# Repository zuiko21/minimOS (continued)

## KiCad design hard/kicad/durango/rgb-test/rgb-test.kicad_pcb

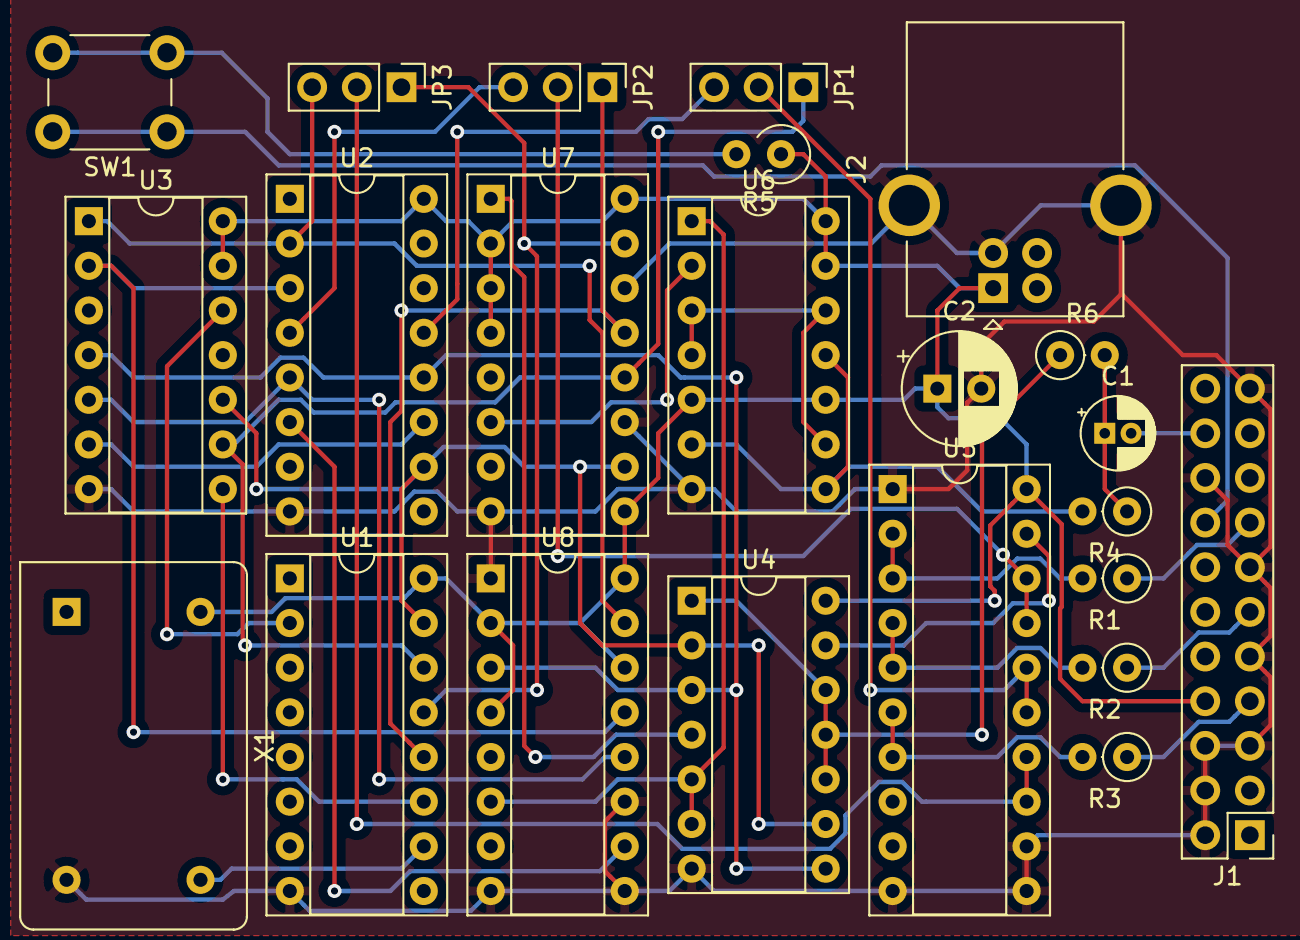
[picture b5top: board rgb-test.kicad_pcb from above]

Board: 2 copper layers, 23 parts (0 on the bottom side), 37 nets.

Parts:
C1: 100uF; CP_Radial_D4.0mm_P1.50mm
C2: 470uF; CP_Radial_D6.3mm_P2.50mm
J1: SCART; PinHeader_2x11_P2.54mm_Vertical
J2: POWER; USB_B_OST_USB-B1HSxx_Horizontal
JP1: GREEN SEL; PinHeader_1x03_P2.54mm_Vertical
JP2: RED SEL; PinHeader_1x03_P2.54mm_Vertical
JP3: BLUE SEL; PinHeader_1x03_P2.54mm_Vertical
R1, R2, R3: 470; R_Axial_DIN0207_L6.3mm_D2.5mm_P2.54mm_Vertical
R4: 1K2; R_Axial_DIN0207_L6.3mm_D2.5mm_P2.54mm_Vertical
R5: 180; R_Axial_DIN0309_L9.0mm_D3.2mm_P2.54mm_Vertical
R6: 1K5; R_Axial_DIN0207_L6.3mm_D2.5mm_P2.54mm_Vertical
SW1: TEST; SW_PUSH_6mm
U1: 74HCT4040; DIP-16_W7.62mm_Socket
U2: 74HC4040; DIP-16_W7.62mm_Socket
U3: 74HC21; DIP-14_W7.62mm_Socket
U4: 74HC02; DIP-14_W7.62mm_Socket
U5: 74HC245; DIP-20_W7.62mm_Socket
U6: 74HC86; DIP-14_W7.62mm_Socket
U7, U8: 74HC85; DIP-16_W7.62mm_Socket
X1: 24.576 MHz; Oscillator_DIP-14

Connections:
+5V: C2.1, J1.8, J2.1, R5.1, U1.16, U2.16, U3.13, U3.14, U4.14, U5.20, U6.5, U6.10, U6.13, U6.14, U7.2, U7.3, U7.4, U7.9, U7.16, U8.2, U8.4, U8.14, U8.16, X1.14
/BIN: JP3.2, U5.13, U5.14
/BLUE: R3.2, U5.6, U5.7
/COMP: C1.2, J1.20
/CSYNC: U6.3, U6.4, U6.9, U6.12
/DE: R6.1, U4.1, U4.10, U4.11, U4.12
/FB: J1.16, SW1.1
/FEND: U2.11, U3.6
/GIN: JP1.2, U5.15, U5.16
/GREEN: R2.2, U5.4, U5.5
/H0: JP3.1, U1.13, U7.15
/H1: JP2.1, U1.12, U7.13
/H2: JP1.1, U1.14, U3.9, U7.12
/HS: U6.2, U7.6
/LEND: U1.11, U3.8
/RED: R1.2, U5.2, U5.3
/RIN: JP2.2, U5.17, U5.18
/S_B: J1.7, R3.1
/S_G: J1.11, R2.1
/S_R: J1.15, R1.1
/V0: JP3.3, U2.2, U3.1, U8.15
/V1: JP2.3, U2.4
/V2: JP1.3, U2.13
/VA1: U1.2, U3.12
/VS: U4.5, U4.6, U6.1, U8.6
/~CSYNC: R4.2, U6.6, U6.8, U6.11
/~DE: U4.13, U5.19
/~DEH: U1.15, U2.10, U3.10, U4.2, U4.9, U7.10
/~DEV: U2.12, U3.4, U4.3, U4.8, U8.3
/~S_SYNC: C1.1, R4.1, R6.2
/~VS: U4.4, U7.1
GND: C2.2, J1.2, J1.4, J1.5, J1.6, J1.9, J1.13, J1.18, J1.21, J2.4, J2.5, U1.8, U2.8, U3.7, U4.7, U5.1, U5.10, U5.11, U5.12, U6.7, U7.8, U7.11, U7.14, U8.1, U8.8, U8.9, U8.11, X1.7
unnamed: R5.2, SW1.2
unnamed: U1.10, X1.8
unnamed: U2.3, U3.2, U8.13
unnamed: U2.5, U3.5, U8.12
unnamed: U2.6, U8.10

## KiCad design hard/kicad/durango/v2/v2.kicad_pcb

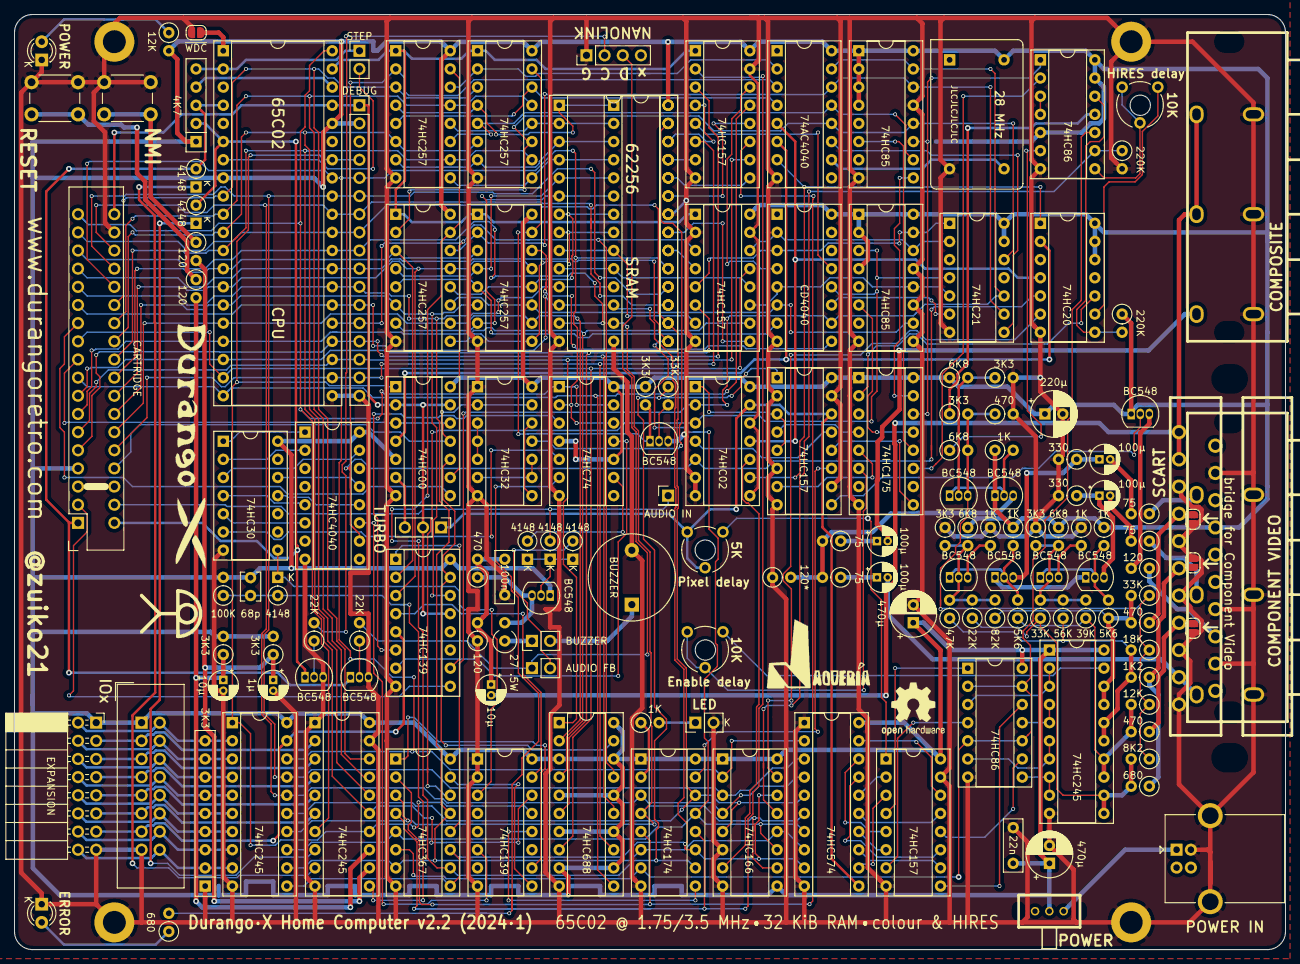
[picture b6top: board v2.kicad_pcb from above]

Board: 2 copper layers, 177.8 x 130.8 mm, 159 parts (0 on the bottom side), 218 nets.

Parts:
BZ1: BUZZER; Buzzer_12x9.5RM7.6
C1, C3: 10µ; CP_Radial_D4.0mm_P1.50mm
C2: 100n; C_Rect_L7.2mm_W2.5mm_P5.00mm_FKS2_FKP2_MKS2_MKP2
C4: 220µ; CP_Radial_D6.3mm_P2.50mm
C5, C611, C612, C709: 100µ; CP_Radial_D4.0mm_P1.50mm
C6, C613: 470µ; CP_Radial_D6.3mm_P2.50mm
C7: 22n; C_Rect_L7.2mm_W2.5mm_P5.00mm_FKS2_FKP2_MKS2_MKP2
C8: 68p; C_Disc_D3.8mm_W2.6mm_P2.50mm
C10: 1µ; CP_Radial_D4.0mm_P1.50mm
D1, D2, D3, D5, D7, D8: 4148; D_DO-35_SOD27_P2.54mm_Vertical_KathodeUp
D4: ERROR; LED_D3.0mm_Clear
D6: POWER; LED_D3.0mm_Clear
H1, H2, H3, H4: MountingHole_3.2mm_M3_DIN965_Pad
J1: NANOLINK; PinHeader_1x04_P2.54mm_Vertical
J2: AUDIO IN; PinHeader_1x01_P2.54mm_Vertical
J3: IOx; IDC-Header_2x08_P2.54mm_Vertical
J4: LED; PinHeader_1x02_P2.54mm_Vertical
J7: POWER IN; USB_B_OST_USB-B1HSxx_Horizontal
J8: DEBUG; PinSocket_1x17_P2.54mm_Vertical
J9: CARTRIDGE; PinSocket_2x18_EDGE
J10: STEP; PinHeader_1x02_P2.54mm_Vertical
J11: EXPANSION; PinSocket_2x08_P2.54mm_Horizontal
J605: COMPONENT VIDEO; 3xRCA
J706: COMPOSITE; 3xRCA
J905: SCART
JP1: AUDIO FB; PinHeader_1x02_P2.54mm_Vertical
JP2: BUZZER; PinHeader_1x02_P2.54mm_Vertical
JP3: POWER; PowerSwitch
JP4: ~WDC; SolderJumper-2_P1.3mm_Open_RoundedPad1.0x1.5mm
JP5: TURBO; PinHeader_1x03_P2.54mm_Vertical
JP606: bridge for Component Video; SolderJumper-2_P1.3mm_Open_RoundedPad1.0x1.5mm
JP607, JP608: CV; SolderJumper-2_P1.3mm_Open_RoundedPad1.0x1.5mm
LOGO1: OSHW-Logo2_9.8x8mm_SilkScreen
LOGO2: durango-x90
LOGO3: jaqueria
Q1, Q2, Q3, Q4, Q5, Q307, Q608, Q609, Q610, Q611, Q906: BC548; TO-92_Inline
R1, R2, R644: 22K; R_Axial_DIN0207_L6.3mm_D2.5mm_P2.54mm_Vertical
R3, R18, R34, R220, R337, R639, R649: 3K3; R_Axial_DIN0207_L6.3mm_D2.5mm_P2.54mm_Vertical
R4, R21, R112, R114: 470; R_Axial_DIN0207_L6.3mm_D2.5mm_P2.54mm_Vertical
R5, R33, R35, R922: 120; R_Axial_DIN0207_L6.3mm_D2.5mm_P2.54mm_Vertical
R6, R111: 680; R_Axial_DIN0207_L6.3mm_D2.5mm_P2.54mm_Vertical
R15: 120*; R_Axial_DIN0207_L6.3mm_D2.5mm_P2.54mm_Vertical
R16, R32, R640, R641, R650, R651: 1K; R_Axial_DIN0207_L6.3mm_D2.5mm_P2.54mm_Vertical
R17, R19, R638, R648: 6K8; R_Axial_DIN0207_L6.3mm_D2.5mm_P2.54mm_Vertical
R23: 27 .5W; R_Axial_DIN0309_L9.0mm_D3.2mm_P2.54mm_Vertical
R26: 100K; R_Axial_DIN0207_L6.3mm_D2.5mm_P2.54mm_Vertical
R29, R108: 12K; R_Axial_DIN0207_L6.3mm_D2.5mm_P2.54mm_Vertical
R30, R647, R657, R731: 75; R_Axial_DIN0207_L6.3mm_D2.5mm_P2.54mm_Vertical
R107: 8K2; R_Axial_DIN0207_L6.3mm_D2.5mm_P2.54mm_Vertical
R109: 18K; R_Axial_DIN0207_L6.3mm_D2.5mm_P2.54mm_Vertical
R110, R336, R654: 33K; R_Axial_DIN0207_L6.3mm_D2.5mm_P2.54mm_Vertical
R113: 1K2; R_Axial_DIN0207_L6.3mm_D2.5mm_P2.54mm_Vertical
R642, R652: 330; R_Axial_DIN0207_L6.3mm_D2.5mm_P2.54mm_Vertical
R643, R653: 5K6; R_Axial_DIN0207_L6.3mm_D2.5mm_P2.54mm_Vertical
R645: 47K; R_Axial_DIN0207_L6.3mm_D2.5mm_P2.54mm_Vertical
R646: 82K; R_Axial_DIN0207_L6.3mm_D2.5mm_P2.54mm_Vertical
R655: 56K; R_Axial_DIN0207_L6.3mm_D2.5mm_P2.54mm_Vertical
R656: 39K; R_Axial_DIN0207_L6.3mm_D2.5mm_P2.54mm_Vertical
R824, R825: 220K; R_Axial_DIN0207_L6.3mm_D2.5mm_P2.54mm_Vertical
RN1: 4K7; R_Array_SIP5
RN2: 3K3; R_Array_SIP9
RV127: 5K; Potentiometer_Piher_PT-6-V_Vertical
RV128, RV231: 10K; Potentiometer_Piher_PT-6-V_Vertical
SW1: RESET; SW_PUSH_6mm
SW2: NMI; SW_PUSH_6mm
U1: 65C02; DIP-40_W15.24mm_Socket
U003: 62256; DIP-28_W7.62mm_Socket
U3: 62256; DIP-28_W15.24mm_Socket
U6, U7, U125, U321: 74HC157; DIP-16_W7.62mm_Socket
U8: 74HC30; DIP-14_W7.62mm_Socket
U9: 74HC00; DIP-14_W7.62mm_Socket
U10, U29: 74HC139; DIP-16_W7.62mm_Socket
U11: 74HC688; DIP-20_W7.62mm_Socket
U12: 74HC74; DIP-14_W7.62mm_Socket
U13: 74HC32; DIP-14_W7.62mm_Socket
U14: 74HC4040; DIP-16_W7.62mm_Socket
U15: 74AC4040; DIP-16_W7.62mm_Socket
U16: 74HC02; DIP-14_W7.62mm_Socket
U17: 74HC21; DIP-14_W7.62mm_Socket
U18, U20: 74HC85; DIP-16_W7.62mm_Socket
U19: CD4040; DIP-16_W7.62mm_Socket
U22: 74HC175; DIP-16_W7.62mm_Socket
U23, U126: 74HC86; DIP-14_W7.62mm_Socket
U31, U32, U127: 74HC245; DIP-20_W7.62mm_Socket
U104, U105, U204, U205: 74HC257; DIP-16_W7.62mm_Socket
U124: 74HC574; DIP-20_W7.62mm_Socket
U224: 74HC166; DIP-16_W7.62mm_Socket
U227: 74HC20; DIP-14_W7.62mm_Socket
U428: 74HC174; DIP-16_W7.62mm_Socket
U530: 74HC367; DIP-16_W7.62mm_Socket
X1: 28 MHz; Oscillator_DIP-14

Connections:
+5V: C4.1, C6.1, C7.1, C8.2, C613.1, J3.1, J8.2, J9.7, J11.1, J905.8, JP3.2, Q3.1, Q5.1, Q609.1, Q611.1, Q906.1, R3.2, R16.1, R17.1, R26.2, R29.2, R34.2, R337.1, R638.1, R641.1, R648.1, R651.1, R825.1, RN1.1, U1.8, U1.36, U003.28, U3.28, U6.16, U7.16, U8.14, U9.5, U9.14, U10.16, U11.3, U11.5, U11.7, U11.9, U11.12, U11.14, U11.16, U11.18, U11.20, U12.4, U12.10, U12.14, U13.14, U14.16, U15.16, U16.14, U17.13, U17.14, U18.1, U18.2, U18.3, U18.4, U18.16, U19.16, U20.1, U20.2, U20.4, U20.16, U22.1, U22.16, U23.5, U23.13, U23.14, U29.16, U31.20, U32.20, U104.16, U105.16, U124.20, U125.16, U126.14, U127.1, U127.20, U204.16, U205.16, U224.1, U224.9, U224.16, U227.12, U227.13, U227.14, U321.16, U428.1, U428.16, U530.16, X1.14
/250HZ: U14.11, U29.6
/ABUF: Q3.3, R4.1, R23.2
/AFB: D7.2, JP1.2
/AFILT: C2.1, C3.1, R4.2, R5.2
/AMIX: D2.1, D3.1, D7.1, Q3.2
/AOUT: D2.2, U12.9
/ATBZ: JP2.1, R23.1
/BCL: Q2.2, R2.1
/BDT: Q1.2, R1.1
/BZZ: BZ1.1, JP2.2
/CNT1K: U8.3, U14.15
/CNT2K: U8.1, U14.1
/CNT4: U8.5, U14.6
/CNT8: U8.4, U14.5
/CNT32: U8.2, U14.2
/CNT128: U8.12, U14.13
/CNT256: U8.11, U14.12
/ERRLED: D4.2, R6.1
/HR_B: Q307.2, R336.2
/IEN: U8.6, U12.5
/PHI2: U1.39, U6.1, U7.1, U104.1, U105.1, U204.1, U205.1
/PWLED: D6.2, R29.1
/Power and Extras/+5V_IN: J7.1, JP3.3
/Power and Extras/B_BIAS: Q610.2, R648.2, R649.2, R654.2, R655.2, R656.2
/Power and Extras/B_BUF: C612.1, Q611.3, R652.1
/Power and Extras/EB: Q610.3, R650.2
/Power and Extras/ER: Q608.3, R640.2
/Power and Extras/LED_R: J4.1, R32.2
/Power and Extras/N_SW: R35.1, SW2.2
/Power and Extras/PB: J605.3, R657.1
/Power and Extras/PB_C: C612.2, R657.2
/Power and Extras/PR: J605.1, R647.1
/Power and Extras/PR_C: C611.2, R647.2
/Power and Extras/RMIX2: C709.1, R731.1
/Power and Extras/R_BIAS: Q608.2, R638.2, R639.2, R644.2, R645.2, R646.2
/Power and Extras/R_BUF: C611.1, Q609.3, R642.1
/Power and Extras/R_SW: R33.1, SW1.1
/Power and Extras/UB: Q610.1, Q611.2, R651.2, R653.2
/Power and Extras/UR: Q608.1, Q609.2, R641.2, R643.2
/Power and Extras/Y: C709.2, J706.5
/Power and Extras/~ANMI: C10.1, R34.1, R35.2, U32.12
/Power and Extras/~ARST: C1.1, R3.1, R33.2, U32.13
/Power and Extras/~ST250: C8.1, D5.2, R26.1, U32.11
/RDY: J10.1, RN1.5, U1.2
/SERCLK: J1.2, R2.2
/SERDAT: J1.3, JP1.1, R1.2
/SYNC: J10.2, U1.7
/Video & Clock generation/BIAS: Q4.2, R17.2, R18.1
/Video & Clock generation/BLUE: J905.7, JP608.1, R114.1
/Video & Clock generation/BUFRGB: Q906.3, R922.2
/Video & Clock generation/B_L: U124.12, U125.3
/Video & Clock generation/B_R: U124.16, U125.2
/Video & Clock generation/COLOUR: U321.11, U428.15
/Video & Clock generation/CSYNC: U23.3, U23.4
/Video & Clock generation/DE: U16.1, U321.3, U321.5
/Video & Clock generation/DEV~ODD: RV127.3, U125.1
/Video & Clock generation/DHRDE: U22.2, U227.10
/Video & Clock generation/DHVD: RV231.3, U227.9
/Video & Clock generation/FBLANK: J905.16, R922.1
/Video & Clock generation/FEND: U17.6, U19.11
/Video & Clock generation/GH_L: U124.15, U125.13
/Video & Clock generation/GH_R: U124.19, U125.14
/Video & Clock generation/GL_L: U124.13, U125.10
/Video & Clock generation/GL_R: U124.17, U125.11
/Video & Clock generation/GRN: J905.11, JP607.1, R111.1, R113.1
/Video & Clock generation/HDOT: U16.10, U224.7
/Video & Clock generation/HPIX: R824.1, U23.9, U224.13
/Video & Clock generation/HVG: R220.1, U23.11
/Video & Clock generation/HVID: RV231.1, RV231.2, U23.8
/Video & Clock generation/IB: U126.3, U127.2, U127.3
/Video & Clock generation/IGH: U126.8, U127.8, U127.9
/Video & Clock generation/IGL: U126.11, U127.4, U127.5
/Video & Clock generation/IR: U126.6, U127.6, U127.7
/Video & Clock generation/LATCH: U22.9, U321.12
/Video & Clock generation/LEND: U15.11, U17.8
/Video & Clock generation/MCLK: U15.10, X1.8
/Video & Clock generation/Q1: U15.7, U16.9, U227.1
/Video & Clock generation/Q3: U15.5, U16.11, U227.4
/Video & Clock generation/RED: J905.15, JP606.1, R112.1
/Video & Clock generation/RGB: Q906.2, U321.9
/Video & Clock generation/RMIX: C5.1, R30.1
/Video & Clock generation/R_L: U124.14, U125.6
/Video & Clock generation/R_R: U124.18, U125.5
/Video & Clock generation/UCDE: U22.5, U321.7
/Video & Clock generation/UHDE: U22.4, U321.4
/Video & Clock generation/UHS: U18.6, U22.12
/Video & Clock generation/UVS: U20.6, U22.13
/Video & Clock generation/VIN: Q4.3, R19.2, R21.1, R107.1, R108.1, R109.1, R110.1, R220.2
/Video & Clock generation/VS: U18.9, U22.15
/Video & Clock generation/XB: U125.4, U126.1
/Video & Clock generation/XGH: U125.12, U126.9
/Video & Clock generation/XGL: U125.9, U126.12
/Video & Clock generation/XR: U125.7, U126.4
/Video & Clock generation/ZMIX: Q4.1, Q5.2, R16.2
/Video & Clock generation/~CDE: RV128.1, RV128.2, U22.6
/Video & Clock generation/~CSYNC: R19.1, U23.6
/Video & Clock generation/~DCDE: RV128.3, U127.19
/Video & Clock generation/~FLAGS: U29.12, U428.9
/Video & Clock generation/~HS: U22.11, U23.2
/Video & Clock generation/~HVG: R825.2, U23.12, U227.8
/Video & Clock generation/~LOST: U16.4, U321.13
/Video & Clock generation/~PE: U224.15, U227.6
/Video & Clock generation/~VS: U18.11, U22.14, U23.1
/~FCLK: JP5.3, U9.6
/~HIRES: Q307.1, R337.2, U204.15, U205.15
/~IEN: R6.2, U12.6
/~IO: U9.10, U10.15, U11.19
/~IOAQ: U10.6, U12.3
/~IOBQ: U10.7, U12.11
/~IOQ: U10.1, U10.10
/~SO: RN1.4, U1.38
/~WE1: U13.3, U13.4, U13.5
/~WE2: U13.6, U13.9, U13.10
/~WE3: U13.8, U13.12
A0: J9.26, U1.9, U32.18, U105.3, U205.3
A1: J9.24, U1.10, U32.17, U105.13, U205.13
A2: J9.22, U1.11, U32.16, U105.6, U205.6
A3: J9.20, U1.12, U29.14, U32.15, U105.10, U205.10
A4: J9.18, U1.13, U10.2, U104.3, U204.3
A5: J9.16, U1.14, U10.3, U104.13, U204.13
A6: J9.14, U1.15, U10.14, U104.6, U204.6
A7: J9.12, U1.16, U11.2, U104.10, U204.10
A8: J9.13, U1.17, U6.10, U11.4
A9: J9.15, U1.18, U6.6, U11.6
A10: J9.21, U1.19, U6.13, U11.8
A11: J9.17, U1.20, U7.13, U11.11
A12: J8.16, J9.10, U1.22, U7.6, U11.13
A13: J8.15, J9.11, U1.23, U7.10, U11.1
A14: J8.14, J9.9, U1.24, U7.3, U11.15
A15: J8.13, U1.25, U6.3, U9.9, U11.17
AUDIO: C3.2, J706.1, J706.3, J905.1, J905.3
AUDIO_IN: D3.2, J2.1, J9.4
BA0: J3.3, J11.3, U32.2
BA1: J3.5, J11.5, U32.3
BA2: J3.7, J11.7, U32.4
BA3: J3.9, J11.9, U32.5
BA4: J3.11, J11.11, U32.6
D0: J8.5, J9.28, U1.33, U003.19, U3.19, U12.2, U12.12, U31.18, U124.2, U224.2
D1: J8.6, J9.30, U1.32, U003.18, U3.18, U31.17, U124.3, U224.3
D2: J8.7, J9.32, U1.31, U003.17, U3.17, U31.16, U124.4, U224.4, U428.3
D3: J8.8, J9.33, U1.30, U003.16, U3.16, U31.15, U124.5, U224.5, U428.14
D4: J8.9, J9.31, U1.29, U003.13, U3.13, U31.14, U124.6, U224.10, U428.4, U530.3
D5: J8.10, J9.29, U1.28, U003.15, U3.15, U31.13, U124.7, U224.11, U428.13, U530.5
D6: J8.11, J9.27, U1.27, U003.11, U3.11, U31.12, U124.8, U224.12, U428.6, U530.7, U530.13
D7: J8.12, J9.25, U1.26, U003.12, U3.12, U31.11, U124.9, U224.14, U428.11, U530.9, U530.11
DBLU: R110.2, R114.2, R646.1, R653.1, U127.17, U127.18
DGHI: R107.2, R111.2, R644.1, R654.1, U127.11, U127.12
DGLO: R109.2, R113.2, R645.1, R655.1, U127.15, U127.16
DRED: R108.2, R112.2, R643.1, R656.1, U127.13, U127.14
FCLK: U9.4, U15.6, U227.2
GND: BZ1.2, C1.2, C2.2, C4.2, C6.2, C7.2, C10.2, C613.2, D4.1, D6.1, H1.1, H2.1, H3.1, H4.1, J1.1, J3.15, J4.2, J7.4, J7.5, J8.17, J9.34, J11.15, J605.2, J605.4, J605.6, J706.2, J706.4, J706.6, J905.4, J905.5, J905.9, J905.13, J905.14, J905.17, J905.18, J905.21, JP4.2, JP606.2, JP607.2, JP608.2, Q1.3, Q2.3, Q307.3, R5.1, R15.1, R18.2, R21.2, R639.1, R640.1, R642.2, R649.1, R650.1, R652.2, R824.2, RN2.1, SW1.2, SW2.1, U1.21, U003.14, U3.14, U003.22, U3.22, U6.2, U6.8, U6.15, U7.8, U7.15, U8.7, U9.7, U10.8, U11.10, U12.7, U13.1, U13.7, U14.8, U15.8, U16.6, U16.7, U16.8, U16.12, U17.7, U18.8, U18.13, U19.8, U20.8, U20.9, U20.11, U20.13, U22.8, U23.7, U29.1, U29.2, U29.8, U31.10, U32.1, U32.10, U32.19, U104.8, U105.8, U124.1, U124.10, U125.8, U125.15, U126.7, U127.10, U204.8, U205.8, U224.6, U224.8, U227.7, U321.2, U321.6, U321.8, U321.10, U321.15, U428.8, U530.8, X1.7
HIRES: R336.1, U104.15, U105.15, U321.1, U428.10, U530.10
INVERT: U23.10, U126.2, U126.5, U126.10, U126.13, U428.7, U530.6
LED: R32.1, U428.2
LUMA: C5.2, J605.5, J905.19
MA0: U003.1, U3.1, U105.4, U205.4
MA1: U003.2, U3.2, U105.12, U205.12
MA2: U003.3, U3.3, U105.7, U205.7
MA3: U003.4, U3.4, U105.9, U205.9
MA4: U003.5, U3.5, U104.4, U204.4
MA5: U003.7, U3.7, U104.12, U204.12
MA6: U003.6, U3.6, U104.7, U204.7
MA7: U003.8, U3.8, U104.9, U204.9
MA8: U003.21, U3.21, U6.9
MA9: U003.9, U3.9, U6.7
MA10: U003.10, U3.10, U6.12
MA11: U003.23, U3.23, U7.12
MA12: U003.25, U3.25, U7.7
MA13: U003.24, U3.24, U7.9
MA14: U003.26, U3.26, U7.4
MIX: Q5.3, R15.2, R30.2, R731.2
unnamed: JP4.1, U1.1
PD0: J3.2, J11.2, RN2.9, U31.2
PD1: J3.4, J11.4, RN2.8, U31.3
PD2: J3.6, J11.6, RN2.7, U31.4
PD3: J3.8, J11.8, RN2.6, U31.5
PD4: J3.10, J11.10, RN2.5, U31.6
PD5: J3.12, J11.12, RN2.4, U31.7
PD6: J3.14, J11.14, RN2.3, U31.8
PD7: J3.16, J11.16, RN2.2, U31.9
R~W: J8.4, U1.34, U9.1, U29.13, U31.1, U32.14
SC0: U7.11, U428.5, U530.2
SC1: U7.2, U428.12, U530.4
SCLK: J8.1, J9.36, JP5.2, U1.37, U9.2, U9.13, U10.13
VA0: U14.10, U15.3, U16.5, U105.2, U227.5
VA1: U15.2, U105.14, U205.2
VA2: U15.4, U105.5, U205.14
VA3: U15.13, U18.10, U105.11, U205.5
VA4: U15.12, U17.12, U18.12, U104.2, U205.11
VA5: U15.14, U17.9, U18.14, U104.14, U204.2
VA6: U19.9, U204.14
VA7: U19.7, U104.5, U204.5
VA8: U19.6, U20.10, U104.11, U204.11
VA9: U6.11, U17.5, U19.5, U20.12
VA10: U6.5, U17.1, U19.3, U20.15
VA11: U6.14, U17.2, U19.2, U20.14
VA12: U7.14, U19.4
VA13: U7.5, U19.13
VCLK: JP5.1, RV127.1, RV127.2, U16.13, U124.11, U321.14
~250HZ: D5.1, U8.8, U29.3
~BLANK: U29.9, U530.15
~DWE: U003.27, U3.27, U13.11
~FRAME: U16.3, U17.4, U19.12, U20.3, U530.14
~INTREQ: D1.1, U32.9
~IO8Q: U10.4, U29.15
~IO9Q: J3.13, J11.13, U10.5, U31.19
~IOC: J9.3, U10.9
~IRQ: D1.2, J9.1, Q1.1, RN1.3, U1.4
~LINE: U15.15, U16.2, U17.10, U18.15, U19.10, U530.12
~MCS: U003.20, U3.20, U6.4
~NMI: D8.2, J9.2, Q2.1, RN1.2, U1.6
~NMIREQ: D8.1, U32.8
~RESET: J9.35, U1.40, U12.1, U12.13, U32.7
~ROM_CS: J9.23, U9.8
~ROM_OE: J9.19, U9.3, U9.12
~STAT: U29.10, U530.1
~WE: J9.8, U9.11, U13.2, U13.13

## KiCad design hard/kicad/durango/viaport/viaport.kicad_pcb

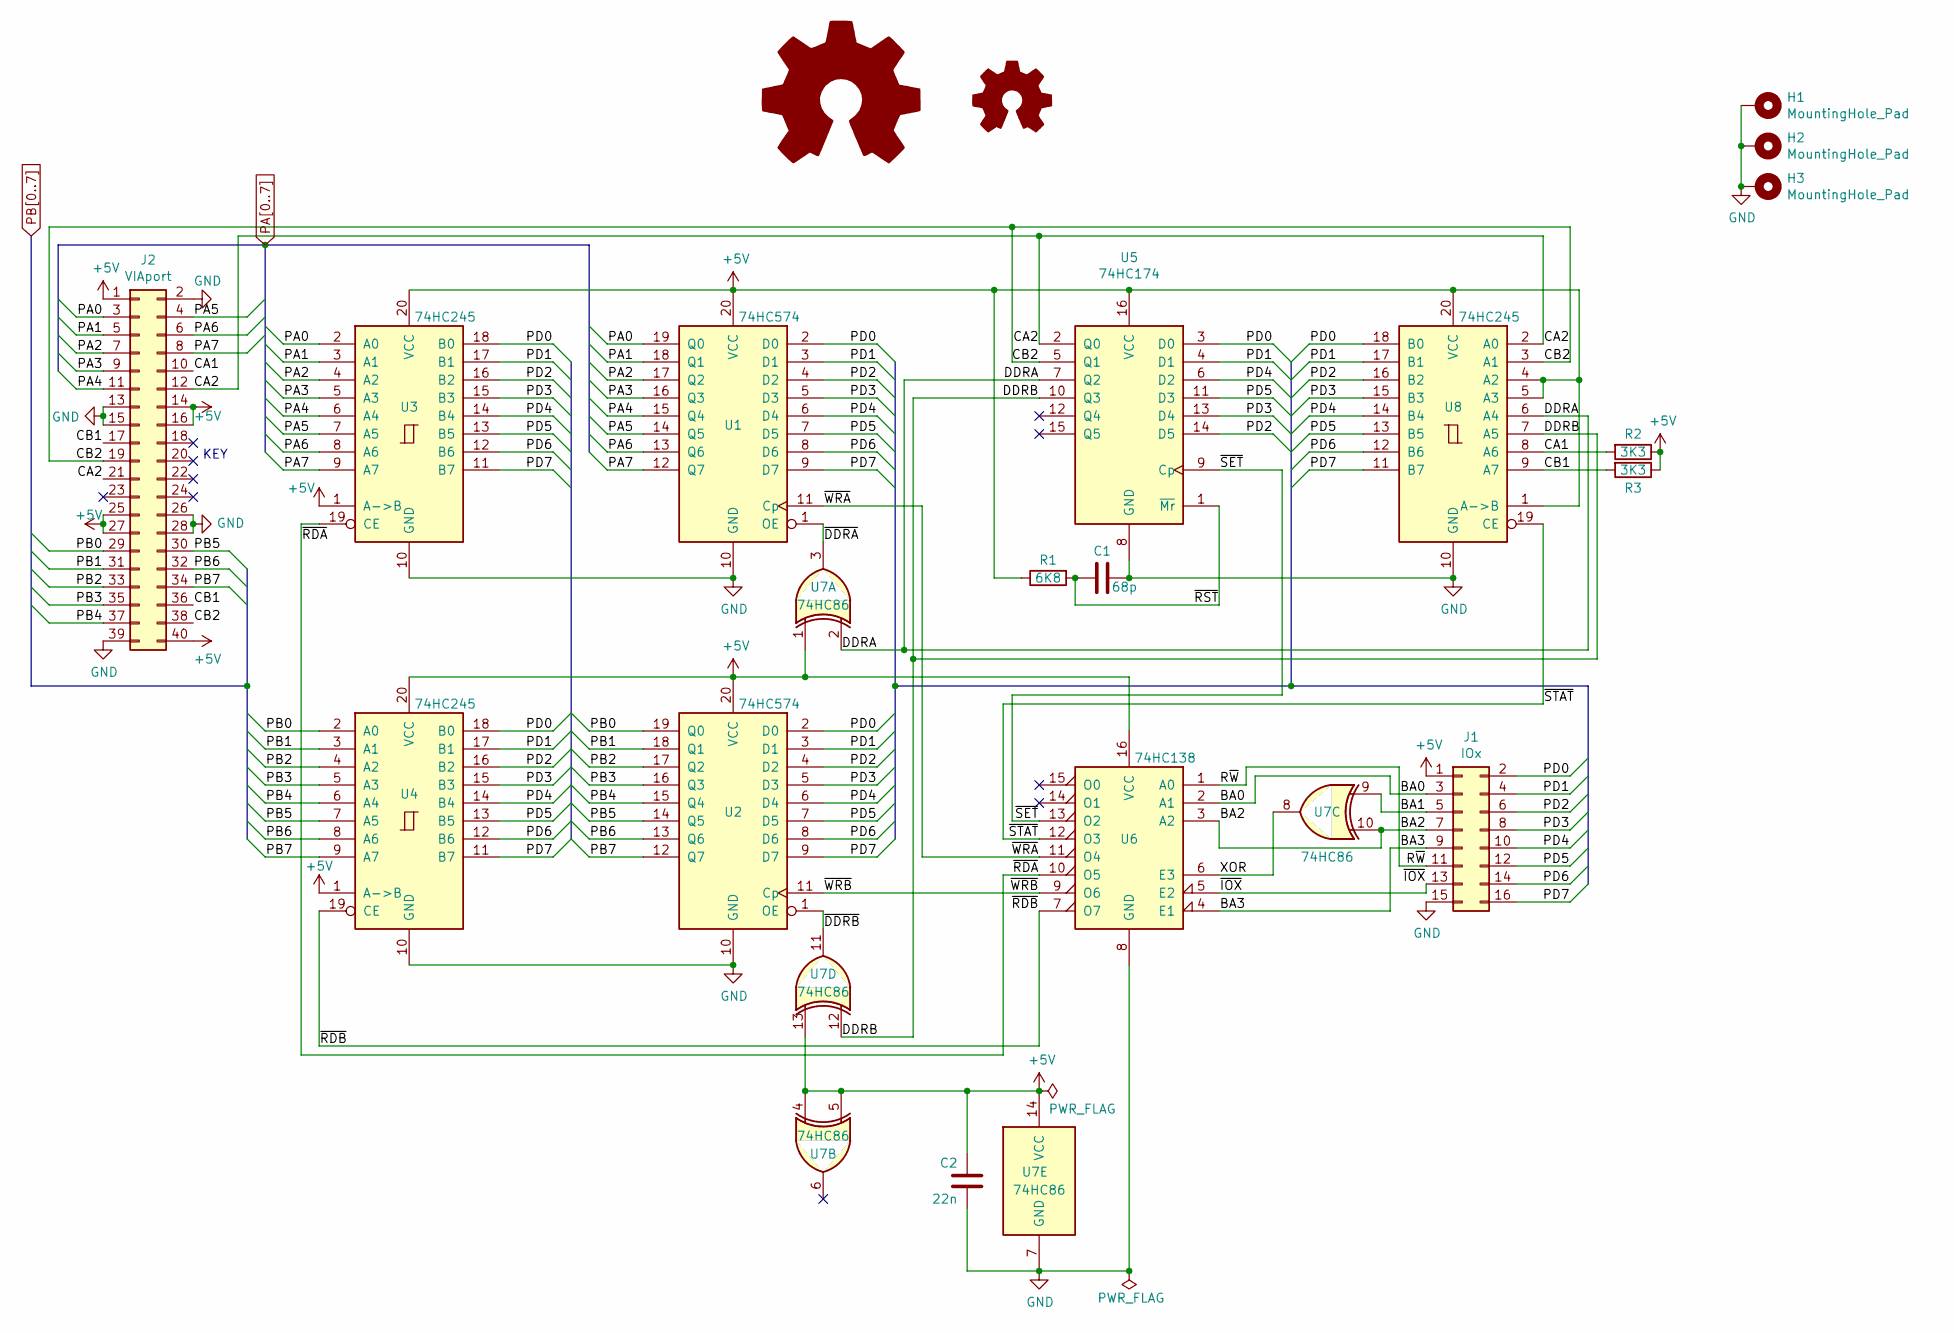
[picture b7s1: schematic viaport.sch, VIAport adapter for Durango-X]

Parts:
C1: 68p; C_Disc_D3.8mm_W2.6mm_P2.50mm
C2: 22n; C_Rect_L7.0mm_W3.5mm_P5.00mm
H1, H2, H3: MountingHole_Pad; MountingHole_3.2mm_M3_DIN965_Pad
J1: IOx; PinHeader_2x08_P2.54mm_Horizontal
J2: VIAport; IDC-Header_2x20_P2.54mm_Vertical
LOGO1: Logo_Open_Hardware_Large; OSHW-Symbol_8.9x8mm_SilkScreen
LOGO2: Logo_Open_Hardware_Small; jaqueria
R1: 6K8; R_Axial_DIN0207_L6.3mm_D2.5mm_P2.54mm_Vertical
R2, R3: 3K3; R_Axial_DIN0207_L6.3mm_D2.5mm_P2.54mm_Vertical
U1, U2: 74HC574; DIP-20_W7.62mm_Socket
U3, U4, U8: 74HC245; DIP-20_W7.62mm_Socket
U5: 74HC174; DIP-16_W7.62mm_Socket
U6: 74HC138; DIP-16_W7.62mm_Socket
U7: 74HC86; DIP-14_W7.62mm_Socket

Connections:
+5V: C2.2, J1.1, J2.1, J2.14, J2.16, J2.25, J2.27, J2.40, R1.1, R2.1, R3.1, U1.20 (VCC), U2.20 (VCC), U3.1 (A->B), U3.20 (VCC), U4.1 (A->B), U4.20 (VCC), U5.16 (VCC), U6.16 (VCC), U7.1, U7.4, U7.5, U7.13, U7.14 (VCC), U8.1 (A->B), U8.4 (A2), U8.5 (A3), U8.20 (VCC)
/BA0: J1.3, U6.2 (A1)
/BA1: J1.5, U7.9
/BA2: J1.7, U6.3 (A2), U7.10
/BA3: J1.9, U6.4 (E1)
/CA1: J2.10, R2.2, U8.8 (A6)
/CA2: J2.12, J2.21, U5.2 (Q0), U8.2 (A0)
/CB1: J2.17, J2.36, R3.2, U8.9 (A7)
/CB2: J2.19, J2.38, U5.5 (Q1), U8.3 (A1)
/DDRA: U5.7 (Q2), U7.2, U8.6 (A4)
/DDRB: U5.10 (Q3), U7.12, U8.7 (A5)
/PD0: J1.2, U1.2 (D0), U2.2 (D0), U3.18 (B0), U4.18 (B0), U5.3 (D0), U8.18 (B0)
/PD1: J1.4, U1.3 (D1), U2.3 (D1), U3.17 (B1), U4.17 (B1), U5.4 (D1), U8.17 (B1)
/PD2: J1.6, U1.4 (D2), U2.4 (D2), U3.16 (B2), U4.16 (B2), U5.14 (D5), U8.16 (B2)
/PD3: J1.8, U1.5 (D3), U2.5 (D3), U3.15 (B3), U4.15 (B3), U5.13 (D4), U8.15 (B3)
/PD4: J1.10, U1.6 (D4), U2.6 (D4), U3.14 (B4), U4.14 (B4), U5.6 (D2), U8.14 (B4)
/PD5: J1.12, U1.7 (D5), U2.7 (D5), U3.13 (B5), U4.13 (B5), U5.11 (D3), U8.13 (B5)
/PD6: J1.14, U1.8 (D6), U2.8 (D6), U3.12 (B6), U4.12 (B6), U8.12 (B6)
/PD7: J1.16, U1.9 (D7), U2.9 (D7), U3.11 (B7), U4.11 (B7), U8.11 (B7)
/R~W: J1.11, U6.1 (A0)
/XOR: U6.6 (E3), U7.8
/~DDRA: U1.1 (OE), U7.3
/~DDRB: U2.1 (OE), U7.11
/~IOX: J1.13, U6.5 (E2)
/~RDA: U3.19 (CE), U6.10 (O5)
/~RDB: U4.19 (CE), U6.7 (O7)
/~RST: C1.2, R1.2, U5.1 (~Mr)
/~SET: U5.9 (Cp), U6.13 (O2)
/~STAT: U6.12 (O3), U8.19 (CE)
/~WRA: U1.11 (Cp), U6.11 (O4)
/~WRB: U2.11 (Cp), U6.9 (O6)
GND: C1.1, C2.1, H1.1, H2.1, H3.1, J1.15, J2.2, J2.13, J2.15, J2.26, J2.28, J2.39, U1.10 (GND), U2.10 (GND), U3.10 (GND), U4.10 (GND), U5.8 (GND), U6.8 (GND), U7.7 (GND), U8.10 (GND)
PA0: J2.3, U1.19 (Q0), U3.2 (A0)
PA1: J2.5, U1.18 (Q1), U3.3 (A1)
PA2: J2.7, U1.17 (Q2), U3.4 (A2)
PA3: J2.9, U1.16 (Q3), U3.5 (A3)
PA4: J2.11, U1.15 (Q4), U3.6 (A4)
PA5: J2.4, U1.14 (Q5), U3.7 (A5)
PA6: J2.6, U1.13 (Q6), U3.8 (A6)
PA7: J2.8, U1.12 (Q7), U3.9 (A7)
PB0: J2.29, U2.19 (Q0), U4.2 (A0)
PB1: J2.31, U2.18 (Q1), U4.3 (A1)
PB2: J2.33, U2.17 (Q2), U4.4 (A2)
PB3: J2.35, U2.16 (Q3), U4.5 (A3)
PB4: J2.37, U2.15 (Q4), U4.6 (A4)
PB5: J2.30, U2.14 (Q5), U4.7 (A5)
PB6: J2.32, U2.13 (Q6), U4.8 (A6)
PB7: J2.34, U2.12 (Q7), U4.9 (A7)

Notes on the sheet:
KEY

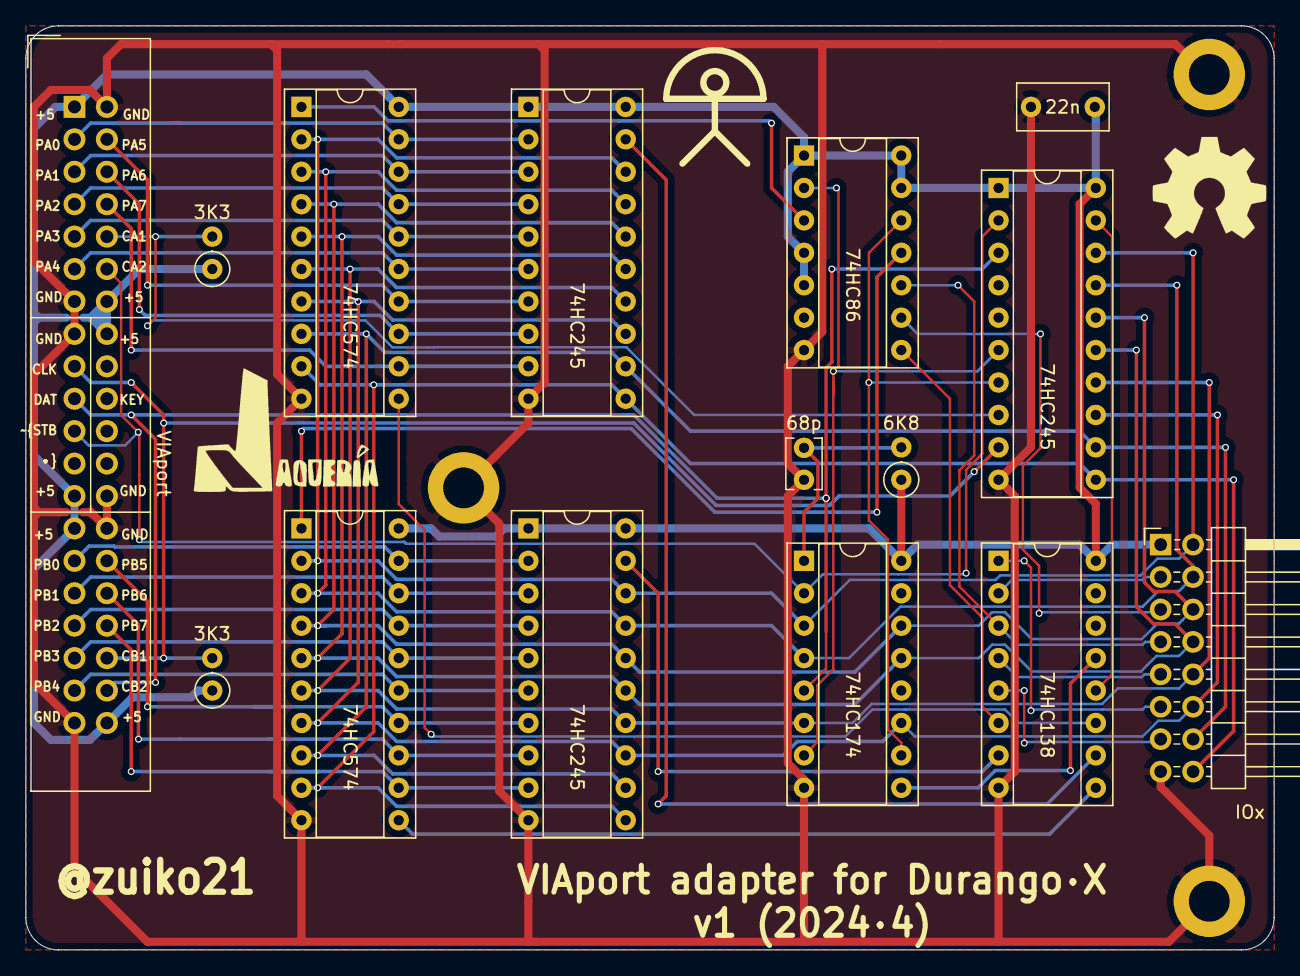
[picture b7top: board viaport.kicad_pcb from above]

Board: 2 copper layers, 97.8 x 72.4 mm, 20 parts (0 on the bottom side), 48 nets.
